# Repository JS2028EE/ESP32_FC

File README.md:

# ESP32_FC — ESP32-S3 quadcopter controller prototype

Rev B is a **70 × 65 mm, four-layer flight-controller hardware prototype** built around an ESP32-S3-WROOM-1-N8R8, a BMI088 SPI inertial sensor and a BMP280 barometer. It is intended for a quadcopter using a separate 4-in-1 ESC. The controller accepts a 3S–6S LiPo supply (9–25.2 V); motor current flows through the ESC.

**Status: unbuilt prototype. No flight firmware is included.** Design-file checks passed in KiCad 10.0.7 on 2026-10-15. No assembled board, power system, ESC interface, control loop or failsafe has been validated. These files support a small prototype order subject to manufacturer DFM acceptance; they do not establish flight or production readiness.

The preview omits some component bodies and is not a complete mechanical model.

## Download and open

1. [Download the complete repository ZIP](https://github.com/JS2028EE/ESP32_FC/archive/refs/heads/main.zip) and extract it.
2. Install KiCad 10 with its standard symbol, footprint and 3D-model libraries.
3. Open [ESP32_FC.kicad_pro](hardware/revB/ESP32_FC.kicad_pro) inside `hardware/revB`. Keep the whole folder together, including its five schematic sheets, local footprint library and `fp-lib-table`.
4. Open the schematic or PCB from KiCad's project manager. In PCB Editor, press **Alt+3** for the 3D Viewer. No standalone STEP assembly is supplied; some model bodies are missing.

For bare-board fabrication, use [ESP32_FC_RevB_Gerbers.zip](downloads/ESP32_FC_RevB_Gerbers.zip) and the [ordering instructions](hardware/revB/Order_Instructions.md). Do not upload the whole repository as a Gerber order. Rev A is superseded.

## Documentation

| Topic | Read |
|---|---|
| Purpose, architecture and intended performance | [System overview](docs/architecture.md) |
| What is missing and what remains untested | [Limitations](docs/limitations.md) |
| All connectors, GPIOs and ESC wiring | [Connections](docs/connections.md) |
| Component selection and buying parts | [Components](docs/components.md) |
| Power rails, load allocations and protection | [Power design](docs/power.md) |
| Firmware requirements and failsafes | [Firmware plan](docs/firmware.md) |
| Dimensions, mounting, layer stack and assembly | [Mechanical and manufacturing](docs/manufacturing.md) |
| Soldering and staged first power-up | [Assembly and bring-up](hardware/revB/Assembly_and_Bringup.md) |
| Checks performed and release boundary | [Validation](hardware/revB/Validation.md) |
| Datasheets and manufacturer references | [Sources](hardware/revB/Sources.md) |
| Revision history | [Change log](CHANGELOG.md) |
| File locations and reproducibility | [Repository guide](docs/repository-guide.md) |
| Contributions and reuse | [Contributing](CONTRIBUTING.md), [licensing status](THIRD_PARTY_NOTICES.md) |

## Main deliverables

- [Schematic PDF, five sheets](hardware/revB/Schematic.pdf) and [assembly drawing](hardware/revB/Assembly_Top.pdf).
- [Editable PCB](hardware/revB/ESP32_FC.kicad_pcb) and [root schematic](hardware/revB/ESP32_FC.kicad_sch).
- [Detailed BOM](hardware/revB/BOM.csv), [grouped shopping list](hardware/revB/Shopping_List.csv), [placement CSV](hardware/revB/Pick_and_place.csv) and [connector pad map](hardware/revB/Connector_Pin_Map.csv).
- [Raw fabrication outputs](hardware/revB/Fabrication), [DRC](hardware/revB/DRC.json), [ERC](hardware/revB/ERC.json), [audit summary](hardware/revB/Design_Audit.json) and [SHA-256 manifest](SHA256SUMS.json).

## Key integration constraints

J5 is a custom **2.54 mm** header and needs a function-matched harness. The reference Holybro Tekko32 F4 4in1 50A AM32 (SKU31102) supports **4S–6S**, so the reference combination starts at 4S. USB is full-speed **12 Mbps, data-only** and needs battery/bench power. Serial logic is 3.3 V. Motor outputs are unidirectional; bidirectional DShot is unsupported. No independent hardware watchdog removes motor enable after a software freeze.

High clock speed is not evidence of a deterministic flight-control loop. A 1 kHz loop is an initial firmware target that must be measured under worst-case load. No stock Betaflight, PX4 or ArduPilot binary is assumed to support this custom board.

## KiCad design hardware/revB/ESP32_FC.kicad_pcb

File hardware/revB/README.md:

# ESP32-S3 flight-controller bench prototype - Rev B

This is the current editable KiCad 10 project for a 70 x 65 mm, four-layer controller, with an ESP32-S3-WROOM-1-N8R8, BMI088 SPI IMU, BMP280 barometer and a separate 4-in-1 ESC. The FC supply accepts a 3S-6S LiPo (9-25.2 V). Motor current stays on the ESC.

**Order status: prepared for a small bare-board prototype run to Order_Instructions.md.** This is an unbuilt design, not validated flight hardware. KiCad checks and the source/PCB audit pass. The manufacturer still must accept the uploaded fabrication data and requested stackup through its normal DFM process. Physical regulator, USB, sensor and flight validation cannot be completed in software. No flight firmware is included.

Use the Rev B ZIP and Gerbers. The earlier Rev A packages are superseded for this build.

## Open the design

Extract the entire project ZIP. Open ESP32_FC.kicad_pro, then ESP32_FC.kicad_sch or ESP32_FC.kicad_pcb. Keep all five schematic files and FC_Prototype.pretty together. In PCB Editor, Alt+3 opens the native 3D Viewer using installed KiCad 10 model libraries. A separate STEP assembly is not bundled. Some bodies are absent in the preview, including the USB connector and the new fuse; model availability does not affect the fabrication data. PCB_Preview.png is a partial 3D illustration, not an exact assembly envelope check.

## What changed

- Added Q3 and R46: USB VBUS now drives an isolated MOSFET gate. GPIO16 is pulled to the MCU's own 3.3 V rail and reads LOW when USB VBUS is present. USB cannot feed the MCU rail through the previous VBUS sense divider. USB remains data-only; battery power is required.
- Added C27, a real 47uF/50V Panasonic radial electrolytic for input damping. C6/C7 are sourced 2.2uF/100V ceramic bypass capacitors, replacing the unsourced 47uF/50V ceramic requirement.
- Selected Littelfuse 0476001.MR, 1 A, with a documented 10 kA interrupt rating at 86 VDC. Its 2410 lands follow the manufacturer drawing; do not fit the old 1206 fuse. This protects the FC branch, not the motor circuit.
- Selected DMN2056U-7 MOSFETs, with on-resistance specified at low gate voltage, for output gating, buzzer and USB detection.
- Changed R21 to 150k. Battery ADC is VIN_PROT/16; 25.2 V at the protected input gives 1.575 V. Calibrate the diode drop and ADC gain in firmware.
- Shortened regulator bootstrap, bypass and feedback routes; connected C8 directly to U3 VIN/PGND. Recorded a JLC04161H-3313 four-layer stackup.
- Rerouted USB D+/D- from ESD protection to the series resistors on the front layer over the uninterrupted ground plane, removing four vias. Those two sections measure 12.960 and 12.945 mm. USB is full speed, 12 Mbps; this is not 480 Mbps USB high speed. Impedance is not a measured/certified result.
- Completed the BOM with selected component numbers, provided a grouped shopping list and a coordinate-based connector map. Stock/price and authorized distributor availability should be checked when buying; substitutions require matching the actual package and electrical characteristics.
- Applied 1.0 mm text height and 0.15 mm text stroke to printed references. 88 references fit on silkscreen; others remain on the assembly layer. Use Assembly_Top.pdf for placement.

## Processor pin assignment

| Function | ESP32-S3 GPIO | Notes |
|---|---|---|
| Battery ADC | 1 | ADC1; senses protected input after D1 |
| ESC current ADC | 2 | ADC1; 2:1 divider, 0-5 V analog input only |
| Motor 1 / 2 / 3 / 4 | 4 / 5 / 6 / 15 | Through U8 and 33-ohm series resistors |
| Gyro / accel data-ready | 7 / 8 | BMI088 INT3 / INT1 |
| Gyro / accel CS | 9 / 10 | Active low; external 10k pull-ups |
| IMU MOSI / SCK / MISO | 11 / 12 / 13 | Separate from the flash/PSRAM interface |
| USB VBUS sense | 16 | Active-low, isolated by Q3 |
| Receiver TX / RX | 17 / 18 | Flight-controller perspective; remapped UART1 |
| USB D- / D+ | 19 / 20 | 22-ohm series termination and USBLC6 protection |
| Arm output | 21 | HIGH enables motor buffers; LOW disables |
| I2C SDA / SCL | 38 / 39 | 4.7k pull-ups to sensor rail |
| Status LED | 40 | HIGH turns LED on |
| Auxiliary GPIO | 41 | Exposed on J9 |
| Active buzzer | 42 | Drives Q2; external 5 V active buzzer <=30 mA |
| Debug TX / RX | 43 / 44 | UART0; includes boot messages |
| GPS TX / RX | 47 / 48 | Remapped UART2 |
| Boot / voltage straps | 0 / 45 / 46 | Boot pull-up, GPIO45/46 pull-downs |

GPIO3 and GPIO14 are unused. GPIO35/36/37 are reserved. Critical sensor buffers and control code should use internal SRAM; do not depend on PSRAM access latency for the real-time loop. A reasonable initial firmware target is a 1 kHz gyro-triggered loop, subject to measured worst-case latency. Hardware peripherals should generate motor timing. Radio operation, flash writes, USB, and navigation tasks must be qualified for scheduling interference.

## Connectors and ESC

Connector_Pin_Map.csv gives every numbered header pad and its location as viewed from the component side, with the antenna at the top. It is the definitive pad-to-net map. J5 uses 2.54 mm headers, not the 1 mm connector fitted to commercial ESCs. A custom harness is required.

| Connector | Pins in numeric order |
|---|---|
| J2 | battery+, GND; FC branch supply only |
| J3 | GND, sensor 3.3V, SDA, SCL |
| J4 | ARM_GATE, GND; short to force outputs disabled |
| J5 | GND, battery+, motor1, motor2, motor3, motor4, analog current, telemetry breakout |
| J6 | GND, 5V, FC RX, FC TX; receiver |
| J7 | GND, 5V, FC RX, FC TX; GPS |
| J8 | GND, digital 3.3V, FC RX0, FC TX0; debug |
| J9 | GND, digital 3.3V, GPIO41, telemetry breakout |
| J10 | 5V, buzzer low-side drain |

J2 and J5 battery pins are the same node. Use only one FC battery feed. Receiver/GPS supply is 5 V but all MCU serial logic is 3.3 V. Do not connect independently powered serial devices or a 5 V UART adapter without checking powered-off and logic-voltage compatibility. J5 analog current accepts 0-5 V and divides it by two. Telemetry is only a passive breakout to J9, not a configured MCU UART.

The reference ESC is Holybro Tekko32 F4 4in1 50A AM32, SKU31102; see ESC_Wiring.md. It supports **4S-6S**, so use a 4S pack for that reference combination. The FC itself retains its 3S-6S input range; using 3S requires an ESC explicitly rated for 3S. This recommendation does not establish motor/propeller compatibility; motor current requirements must be matched separately.

## Power and firmware limits

The 5 V regulator is rated 1 A; it supplies all downstream rails and peripherals. Initial allocations: digital 3.3 V <=0.70 A, sensor 3.3 V <=0.05 A, external 5 V <=0.25 A including buzzer. They correspond to about 0.84 A from 5 V at 85% digital-buck efficiency. These are design allocations, not measured continuous ratings. Begin bench tests with smaller loads and verify temperature and transients before approaching them. No VTX/air-unit supply is provided. External active buzzer <=30 mA.

The N8R8 module is specified by Espressif for ambient temperatures up to 65 C, which is lower than the 85 C rating of several passive parts. No board temperature operating range is qualified. Avoid inductors heating the sensors/module. Use the barometer without blocking its pressure port.

Q1 and U8 disable motor outputs during MCU reset. J4 is a physical disable strap. A frozen MCU that leaves ARM asserted is not stopped by independent watchdog hardware: firmware must configure watchdog reset, receiver timeout, arming checks, brownout handling and motor timing. Start with unidirectional DShot300 for ESC bring-up; bidirectional DShot is unsupported through U8. No stock Betaflight/PX4/ArduPilot binary is assumed to work on this custom ESP32 board.

## Before applying power

Follow Assembly_and_Bringup.md. Solder paste and hot-air/reflow are required for the LGA sensors and exposed-pad regulator. Observe component moisture/reflow limits. All components mount on the front; C27 and headers are soldered after reflow. The 6.3 mm diameter C27 body is 11.2 mm tall. Inspect soldering and check resistance to ground before using a current-limited bench supply. Fit the kill strap; leave ESC, motors, receiver and GPS disconnected initially.

## References

See Sources.md for manufacturer documents used for this revision, Order_Instructions.md for fabrication settings and Validation.md for the actual checks and their limits.

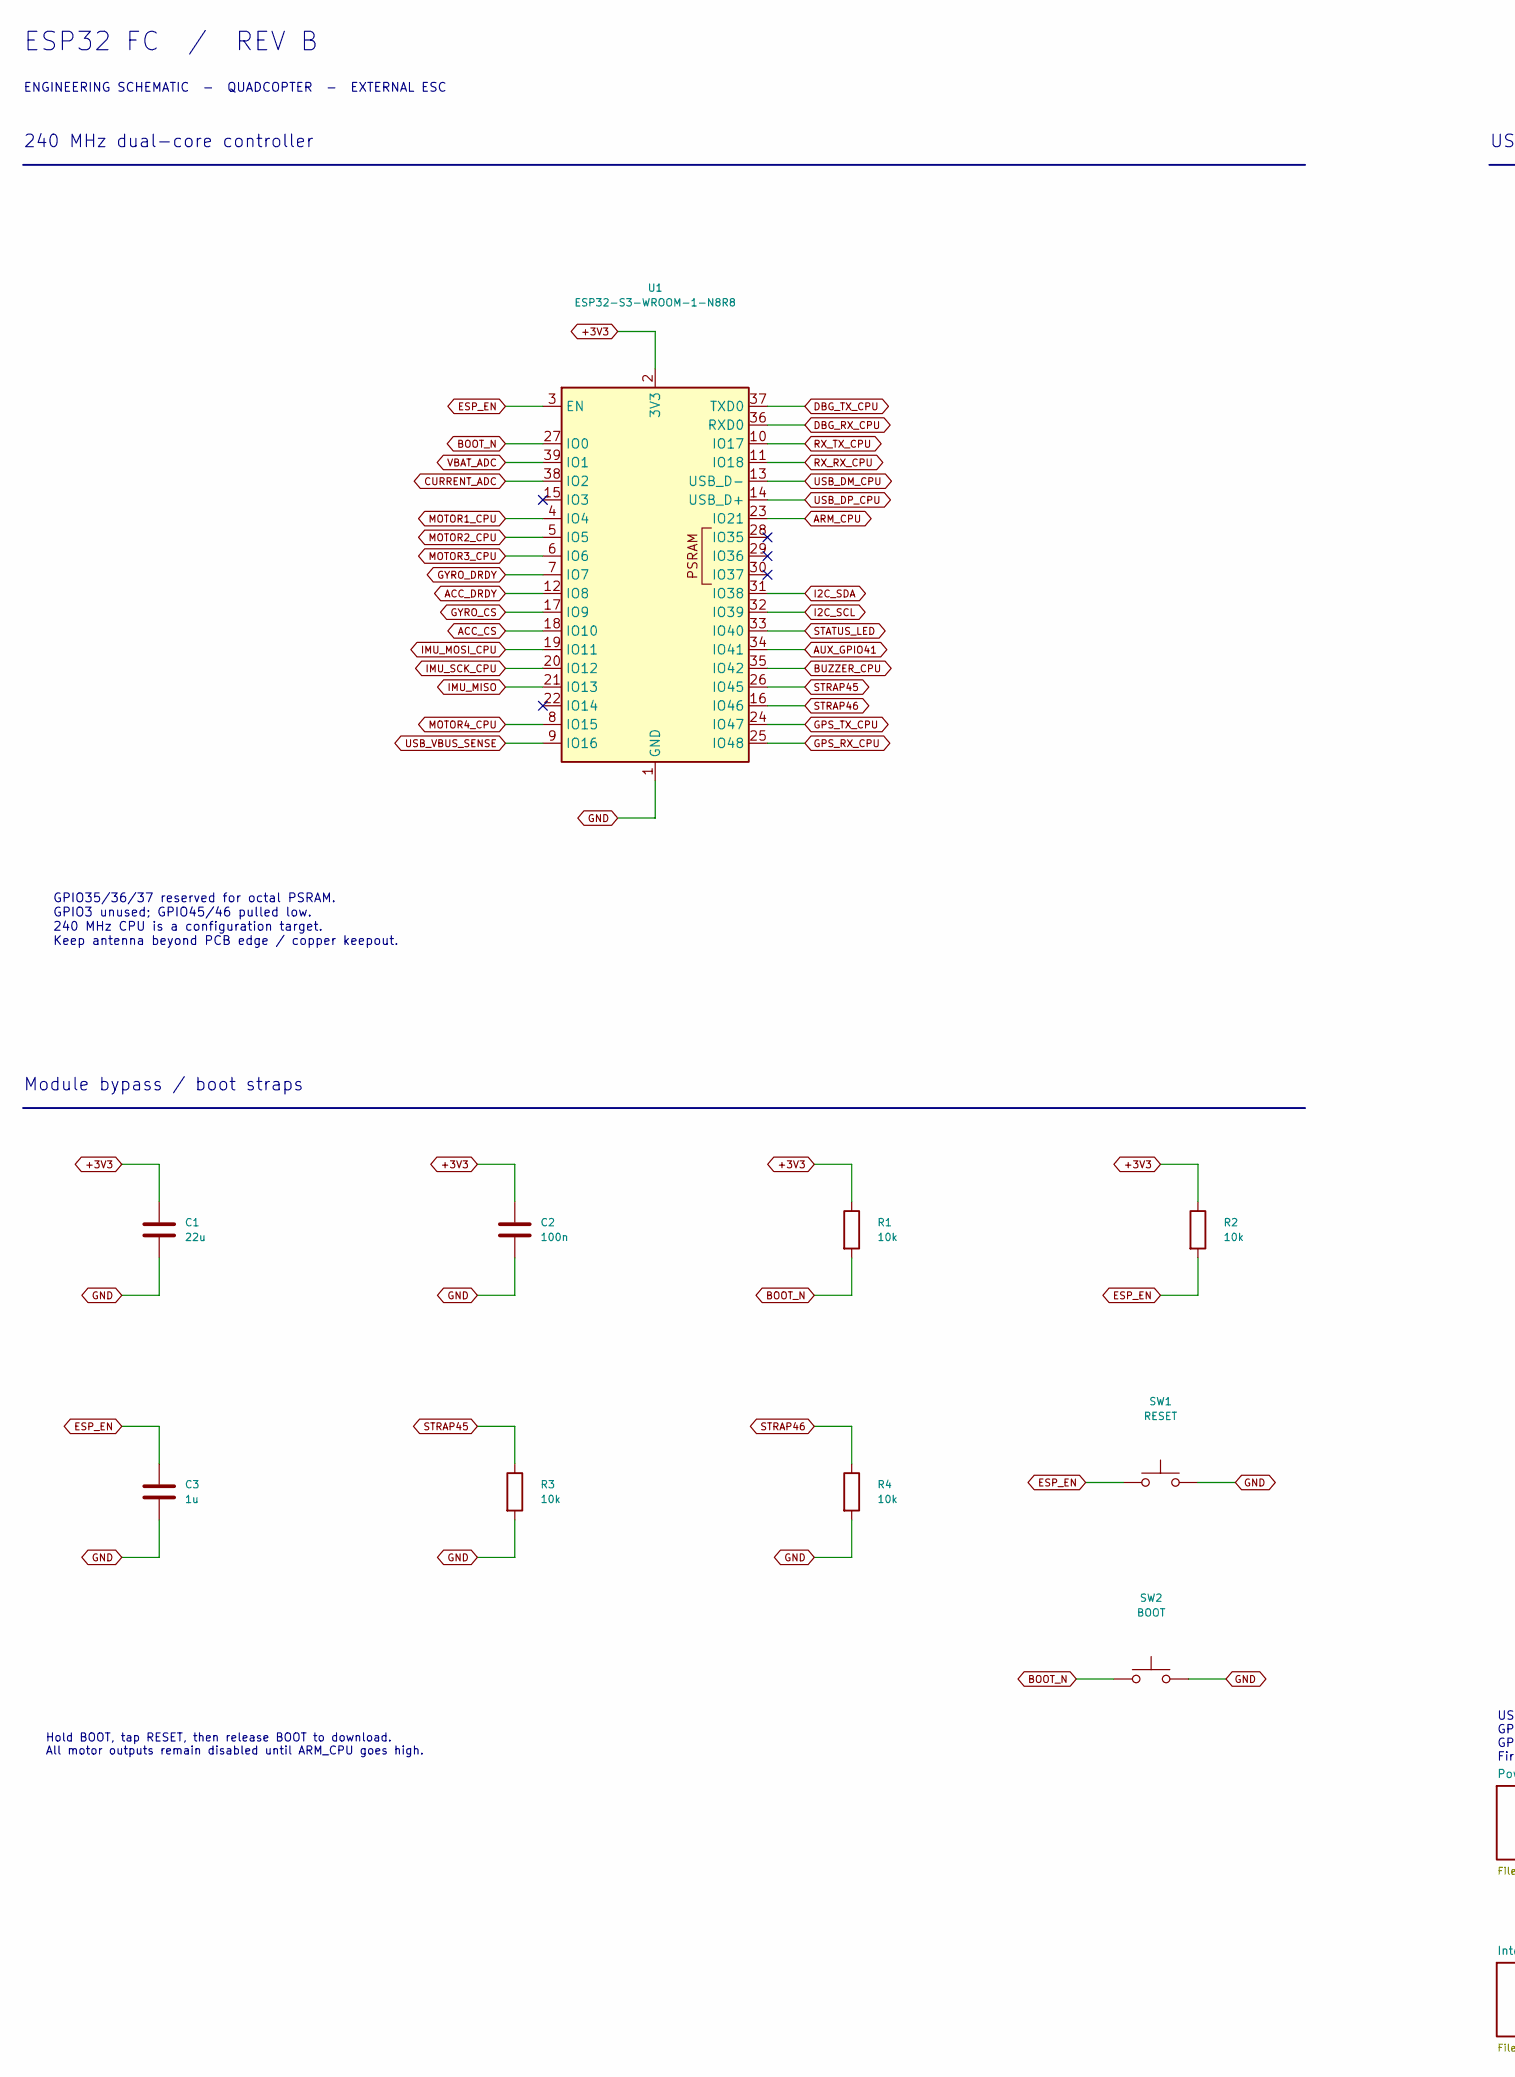
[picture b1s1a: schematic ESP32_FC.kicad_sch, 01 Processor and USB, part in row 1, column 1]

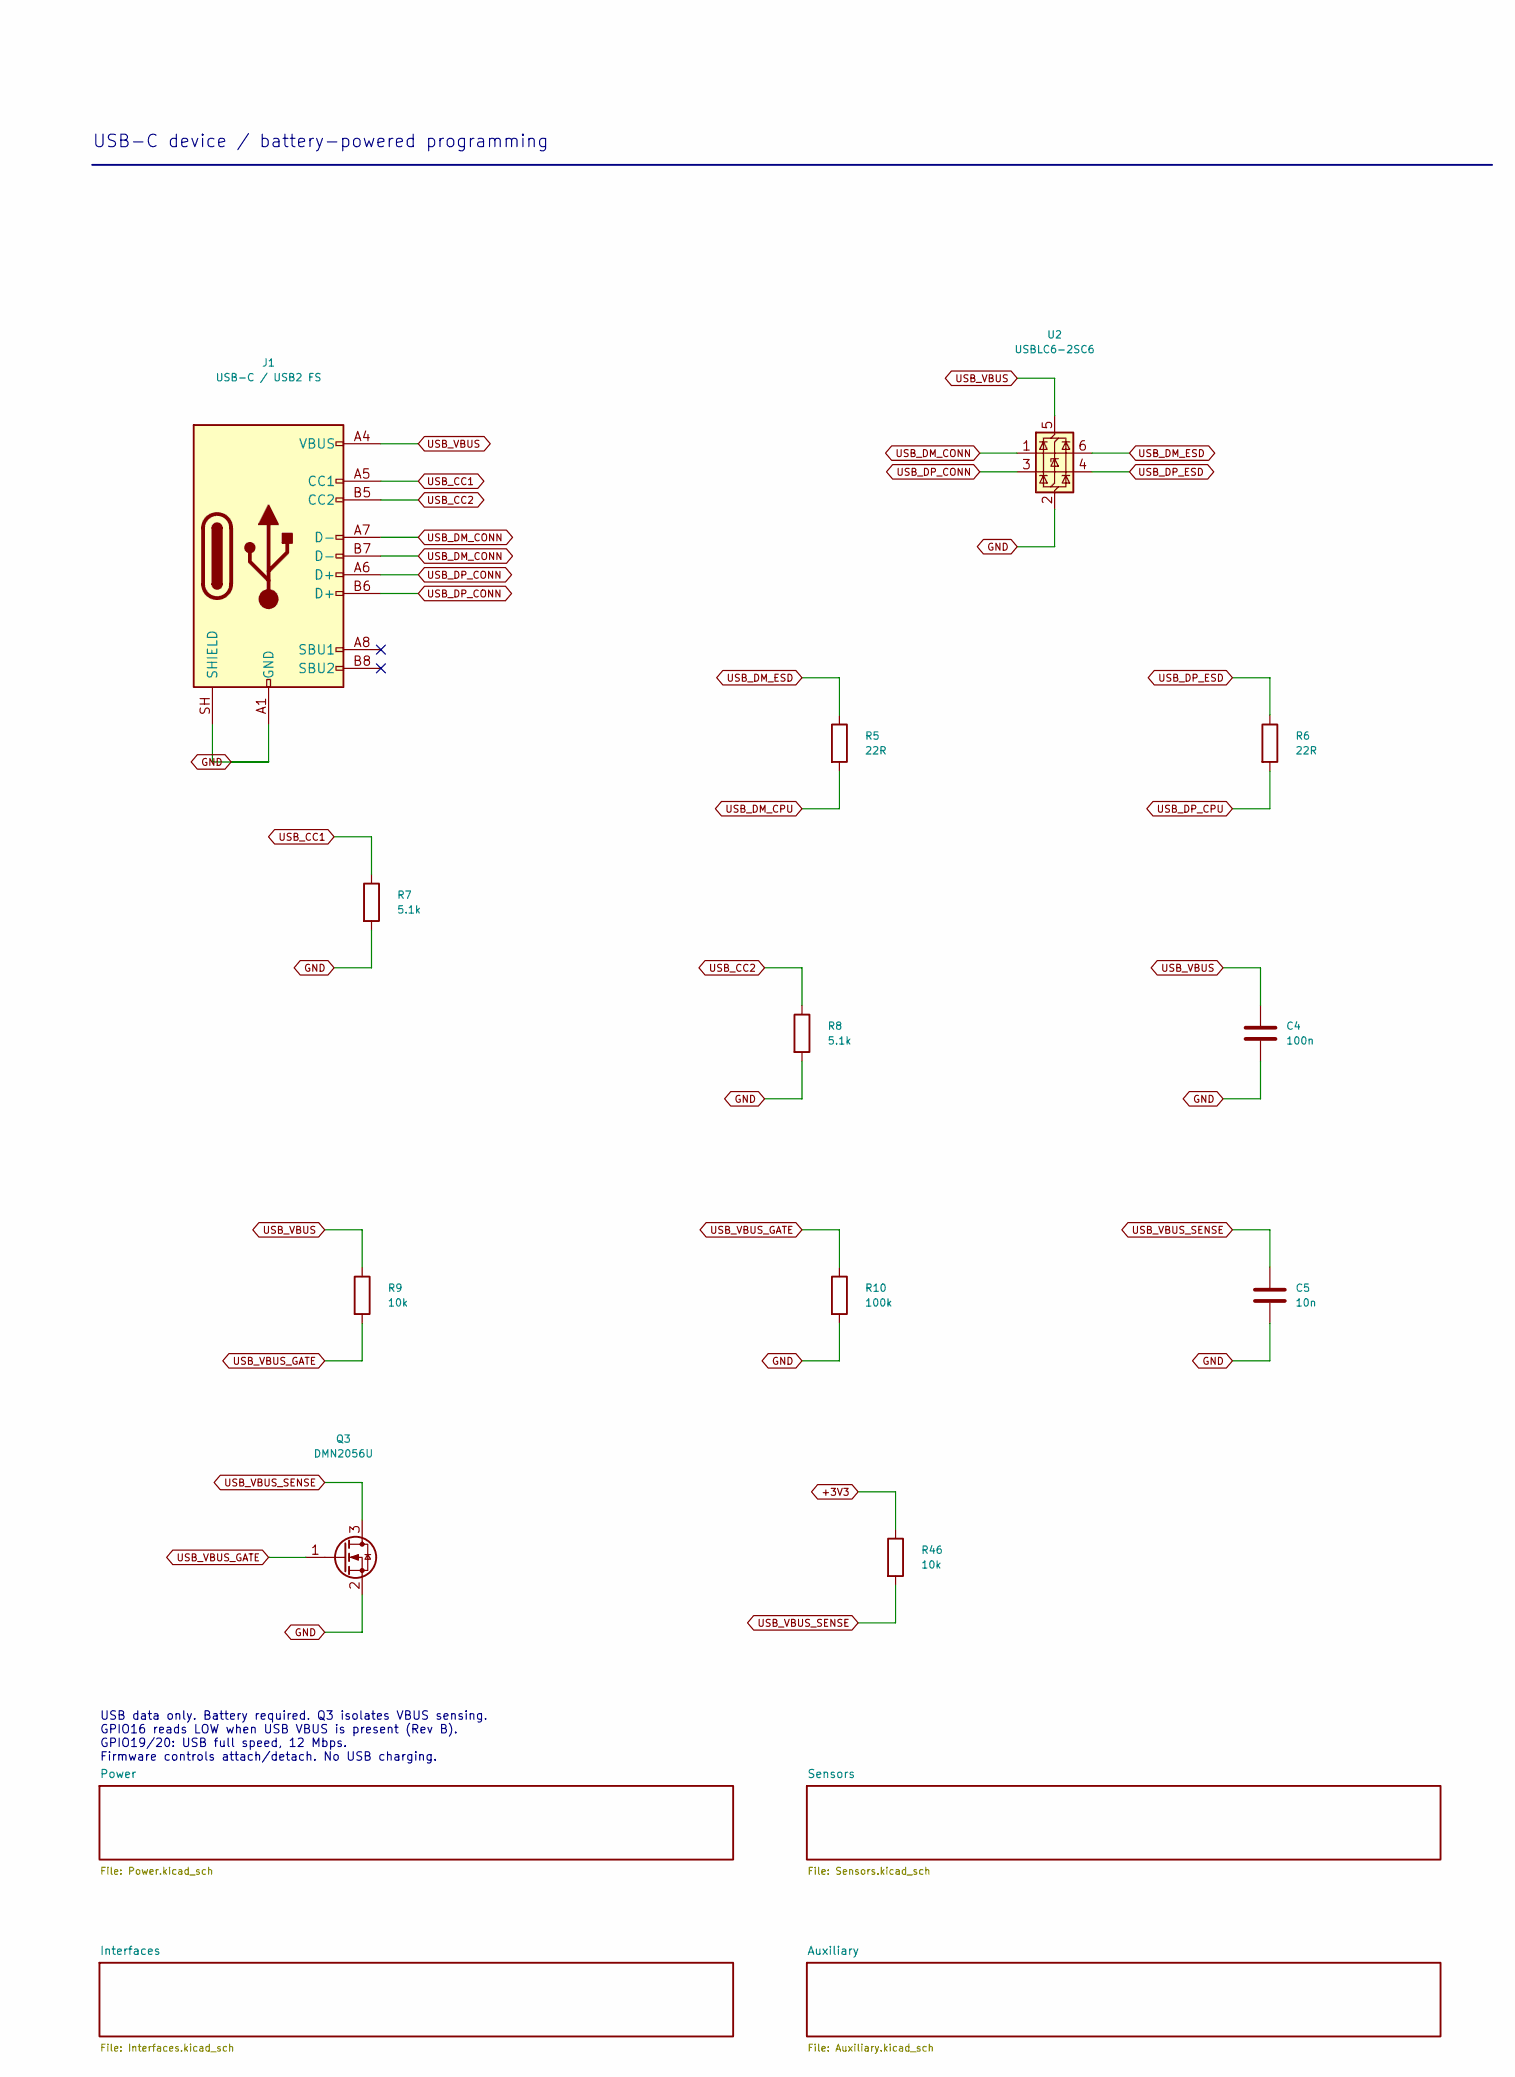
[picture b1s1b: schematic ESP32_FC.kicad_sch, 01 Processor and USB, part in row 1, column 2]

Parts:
C1: 22u; C_0805_2012Metric; MPN GRM21BR61C226ME44L
C2, C4: 100n; C_0603_1608Metric; MPN GRM188R71C104KA01D
C3: 1u; C_0603_1608Metric; MPN GRM188R71C105KA12D
C5: 10n; C_0603_1608Metric; MPN GRM188R71H103KA01D
J1: USB-C / USB2 FS; USB_C_HRO_Edge; MPN TYPE-C-31-M-12
Q3: DMN2056U; SOT-23; MPN DMN2056U-7
R1, R2, R3, R4, R9, R46: 10k; R_0603_1608Metric; MPN RC0603FR-0710KL
R5, R6: 22R; R_0603_1608Metric; MPN RC0603FR-0722RL
R7, R8: 5.1k; R_0603_1608Metric; MPN RC0603FR-075K1L
R10: 100k; R_0603_1608Metric; MPN RC0603FR-07100KL
SW1: RESET; SW_SPST_TL3342; MPN TL3342F160QG
SW2: BOOT; SW_SPST_TL3342; MPN TL3342F160QG
U1: ESP32-S3-WROOM-1-N8R8; ESP32_S3_WROOM_Edge; MPN ESP32-S3-WROOM-1-N8R8
U2: USBLC6-2SC6; SOT-23-6; MPN USBLC6-2SC6

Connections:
+3V3: C1.1, C2.1, R1.1, R2.1, R46.1, U1.2 (3V3); also elsewhere on the board
ACC_CS: U1.18 (IO10); also elsewhere on the board
ACC_DRDY: U1.12 (IO8); also elsewhere on the board
ARM_CPU: U1.23 (IO21); also elsewhere on the board
AUX_GPIO41: U1.34 (IO41); also elsewhere on the board
BOOT_N: R1.2, SW2.1, U1.27 (IO0)
BUZZER_CPU: U1.35 (IO42); also elsewhere on the board
CURRENT_ADC: U1.38 (IO2); also elsewhere on the board
DBG_RX_CPU: U1.36 (RXD0); also elsewhere on the board
DBG_TX_CPU: U1.37 (TXD0); also elsewhere on the board
ESP_EN: C3.1, R2.2, SW1.1, U1.3 (EN)
GND: C1.2, C2.2, C3.2, C4.2, C5.2, J1.A1 (GND), J1.A12 (GND), J1.B1 (GND), J1.B12 (GND), J1.SH (SHIELD), Q3.2 (S), R3.2, R4.2, R7.2, R8.2, R10.2, SW1.2, SW2.2, U1.1 (GND), U1.40 (GND), U1.41 (GND), U2.2 (GND); also elsewhere on the board
GPS_RX_CPU: U1.25 (IO48); also elsewhere on the board
GPS_TX_CPU: U1.24 (IO47); also elsewhere on the board
GYRO_CS: U1.17 (IO9); also elsewhere on the board
GYRO_DRDY: U1.7 (IO7); also elsewhere on the board
I2C_SCL: U1.32 (IO39); also elsewhere on the board
I2C_SDA: U1.31 (IO38); also elsewhere on the board
IMU_MISO: U1.21 (IO13); also elsewhere on the board
IMU_MOSI_CPU: U1.19 (IO11); also elsewhere on the board
IMU_SCK_CPU: U1.20 (IO12); also elsewhere on the board
MOTOR1_CPU: U1.4 (IO4); also elsewhere on the board
MOTOR2_CPU: U1.5 (IO5); also elsewhere on the board
MOTOR3_CPU: U1.6 (IO6); also elsewhere on the board
MOTOR4_CPU: U1.8 (IO15); also elsewhere on the board
RX_RX_CPU: U1.11 (IO18); also elsewhere on the board
RX_TX_CPU: U1.10 (IO17); also elsewhere on the board
STATUS_LED: U1.33 (IO40); also elsewhere on the board
STRAP45: R3.1, U1.26 (IO45)
STRAP46: R4.1, U1.16 (IO46)
USB_CC1: J1.A5 (CC1), R7.1
USB_CC2: J1.B5 (CC2), R8.1
USB_DM_CONN: J1.A7 (D-), J1.B7 (D-), U2.1 (I/O1)
USB_DM_CPU: R5.2, U1.13 (USB_D-)
USB_DM_ESD: R5.1, U2.6 (I/O1)
USB_DP_CONN: J1.A6 (D+), J1.B6 (D+), U2.3 (I/O2)
USB_DP_CPU: R6.2, U1.14 (USB_D+)
USB_DP_ESD: R6.1, U2.4 (I/O2)
USB_VBUS: C4.1, J1.A4 (VBUS), J1.A9 (VBUS), J1.B4 (VBUS), J1.B9 (VBUS), R9.1, U2.5 (VBUS)
USB_VBUS_GATE: Q3.1 (G), R9.2, R10.1
USB_VBUS_SENSE: C5.1, Q3.3 (D), R46.2, U1.9 (IO16)
VBAT_ADC: U1.39 (IO1); also elsewhere on the board

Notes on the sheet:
ESP32 FC / REV B
ENGINEERING SCHEMATIC - QUADCOPTER - EXTERNAL ESC
240 MHz dual-core controller
GPIO35/36/37 reserved for octal PSRAM. GPIO3 unused; GPIO45/46 pulled low. 240 MHz CPU is a configuration target. Keep antenna beyond PCB edge / copper keepout.
Module bypass / boot straps
Hold BOOT, tap RESET, then release BOOT to download. All motor outputs remain disabled until ARM_CPU goes high.
USB-C device / battery-powered programming
USB data only. Battery required. Q3 isolates VBUS sensing. GPIO16 reads LOW when USB VBUS is present (Rev B). GPIO19/20: USB full speed, 12 Mbps. Firmware controls attach/detach. No USB charging.

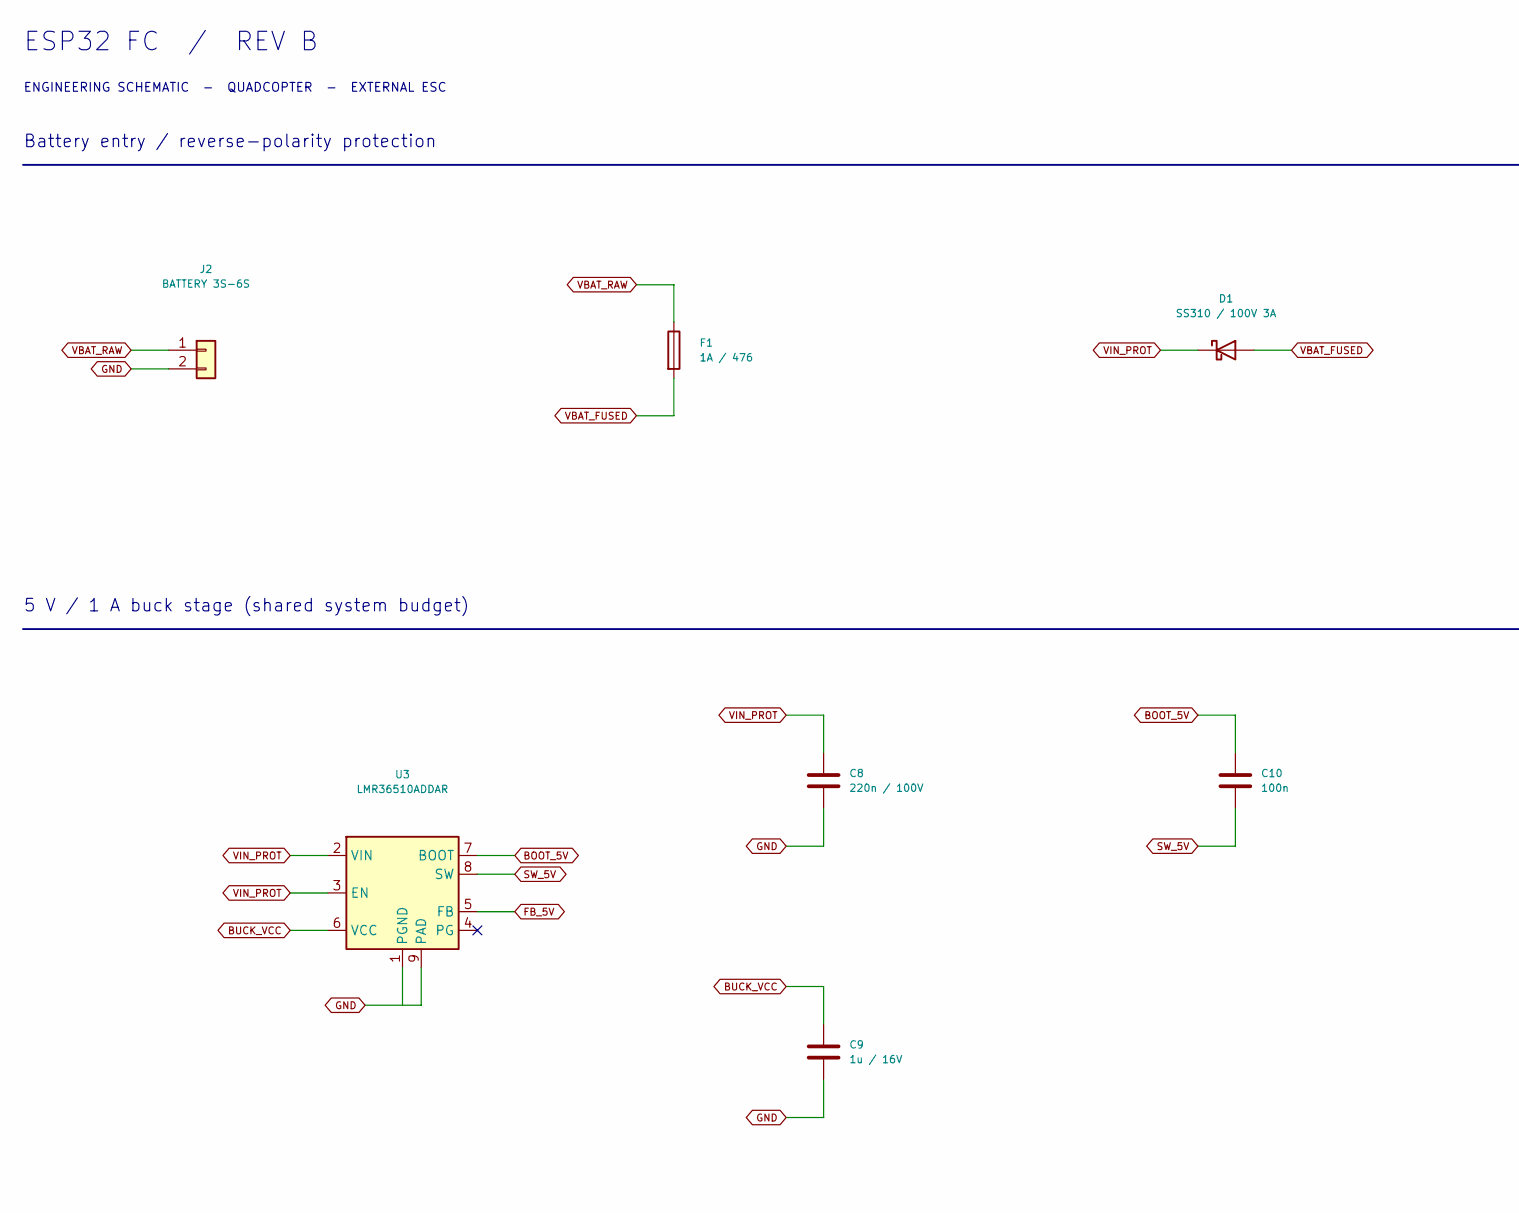
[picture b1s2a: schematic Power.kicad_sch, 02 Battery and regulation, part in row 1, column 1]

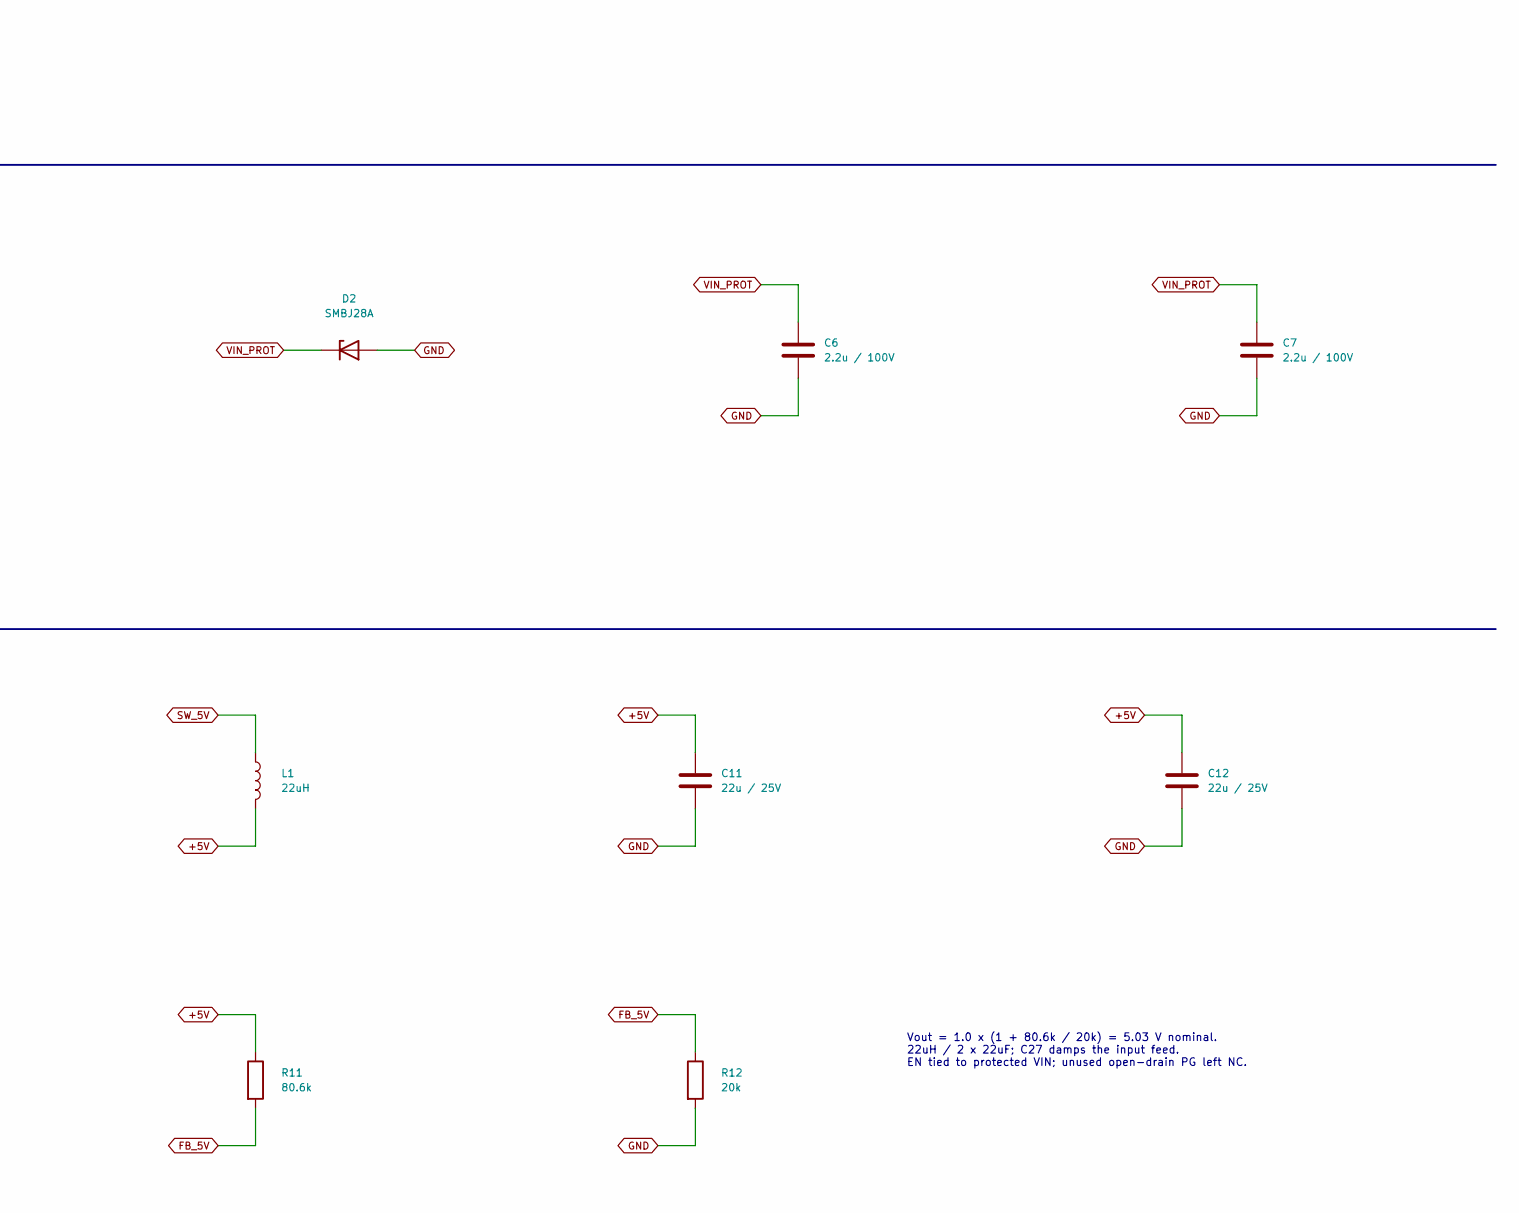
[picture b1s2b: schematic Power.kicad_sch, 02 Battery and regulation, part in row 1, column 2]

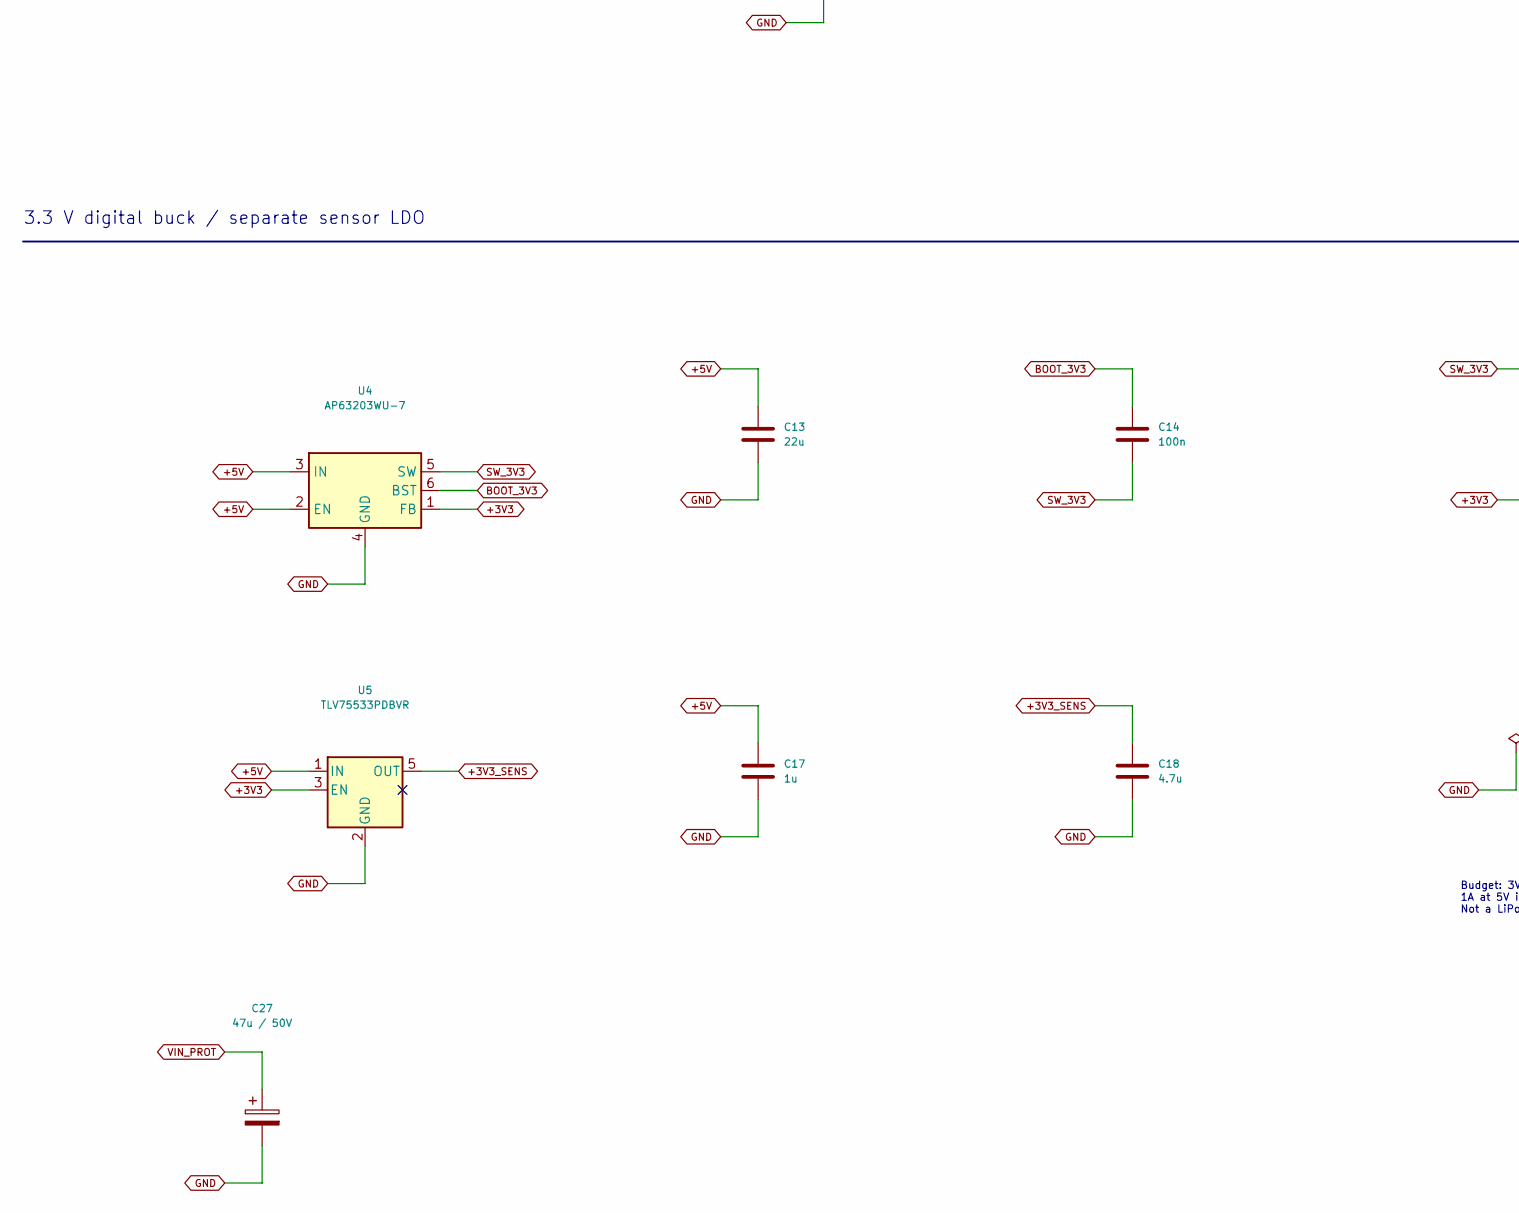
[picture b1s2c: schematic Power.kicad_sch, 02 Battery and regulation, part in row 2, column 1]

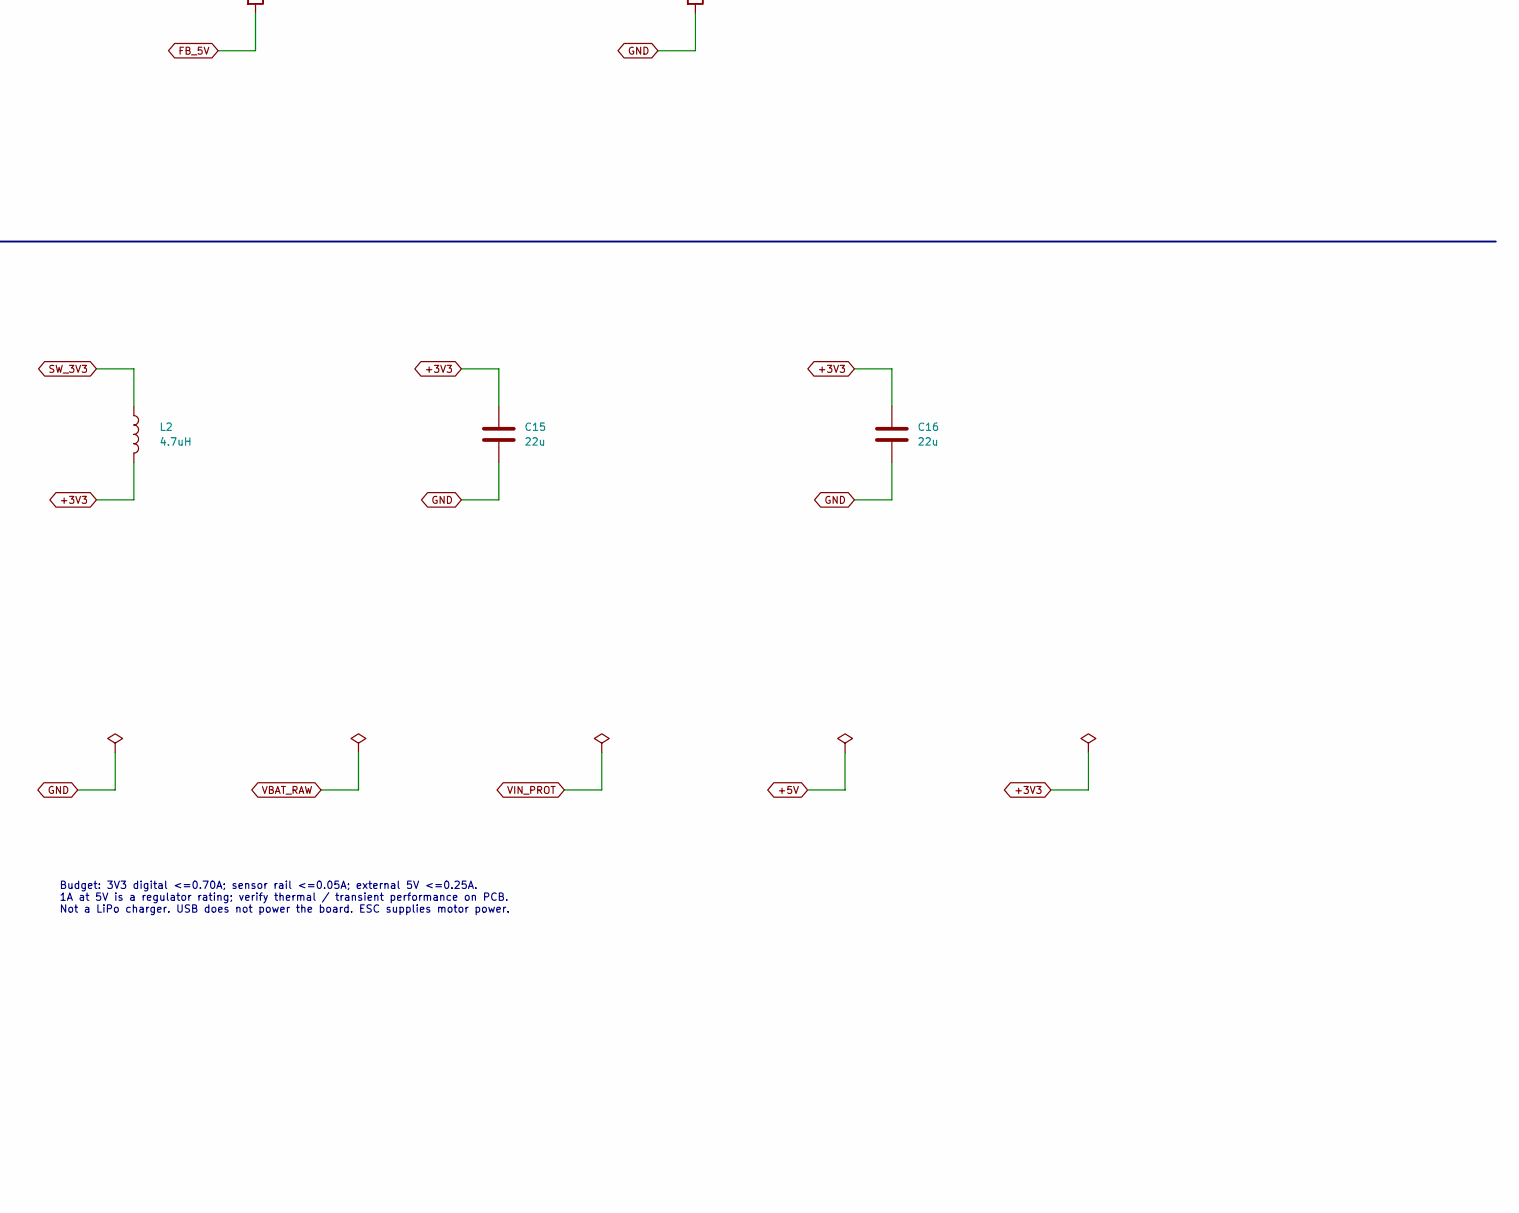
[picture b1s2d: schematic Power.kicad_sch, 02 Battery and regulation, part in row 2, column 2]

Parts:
C6, C7: 2.2u / 100V; C_1210_3225Metric; MPN GRM32ER72A225KA35L
C8: 220n / 100V; C_0805_2012Metric; MPN C0805C224K1RACTU
C9: 1u / 16V; C_0603_1608Metric; MPN GRM188R71C105KA12D
C10, C14: 100n; C_0603_1608Metric; MPN GRM188R71C104KA01D
C11, C12: 22u / 25V; C_1210_3225Metric; MPN GRM32ER71E226KE15L
C13, C15, C16: 22u; C_0805_2012Metric; MPN GRM21BR61C226ME44L
C17: 1u; C_0603_1608Metric; MPN GRM188R71C105KA12D
C18: 4.7u; C_0603_1608Metric; MPN GRM188R61C475KE11D
C27: 47u / 50V; CP_Radial_D6.3mm_P2.50mm; MPN EEUFR1H470
D1: SS310 / 100V 3A; D_SMA; MPN SS310-13-F
D2: SMBJ28A; D_SMB; MPN SMBJ28A-13-F
F1: 1A / 476; Fuse_Littelfuse_476; MPN 0476001.MR
J2: BATTERY 3S-6S; SolderWire-1sqmm_1x02_P5.4mm_D1.4mm_OD2.7mm; MPN WIRE CONNECTION - NO FITTED PART
L1: 22uH; L_Bourns_SRP6060FA; MPN SRP6060FA-220M
L2: 4.7uH; L_Bourns_SRP5030T; MPN SRP5030T-4R7M
R11: 80.6k; R_0603_1608Metric; MPN RC0603FR-0780K6L
R12: 20k; R_0603_1608Metric; MPN RC0603FR-0720KL
U3: LMR36510ADDAR; Texas_HTSOP-8-1EP_3.9x4.9mm_P1.27mm_EP2.95x4.9mm_Mask2.4x3.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; MPN LMR36510ADDAR
U4: AP63203WU-7; TSOT-23-6; MPN AP63203WU-7
U5: TLV75533PDBVR; SOT-23-5; MPN TLV75533PDBVR

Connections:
+3V3: C15.1, C16.1, L2.2, U4.1 (FB), U5.3 (EN); also elsewhere on the board
+3V3_SENS: C18.1, U5.5 (OUT); also elsewhere on the board
+5V: C11.1, C12.1, C13.1, C17.1, L1.2, R11.1, U4.2 (EN), U4.3 (IN), U5.1 (IN); also elsewhere on the board
BOOT_3V3: C14.1, U4.6 (BST)
BOOT_5V: C10.1, U3.7 (BOOT)
BUCK_VCC: C9.1, U3.6 (VCC)
FB_5V: R11.2, R12.1, U3.5 (FB)
GND: C6.2, C7.2, C8.2, C9.2, C11.2, C12.2, C13.2, C15.2, C16.2, C17.2, C18.2, C27.2, D2.2 (A), J2.2, R12.2, U3.1 (PGND), U3.9 (PAD), U4.4 (GND), U5.2 (GND); also elsewhere on the board
SW_3V3: C14.2, L2.1, U4.5 (SW)
SW_5V: C10.2, L1.1, U3.8 (SW)
VBAT_FUSED: D1.2 (A), F1.2
VBAT_RAW: F1.1, J2.1; also elsewhere on the board
VIN_PROT: C6.1, C7.1, C8.1, C27.1, D1.1 (K), D2.1 (K), U3.2 (VIN), U3.3 (EN); also elsewhere on the board

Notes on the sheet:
ESP32 FC / REV B
ENGINEERING SCHEMATIC - QUADCOPTER - EXTERNAL ESC
Battery entry / reverse-polarity protection
5 V / 1 A buck stage (shared system budget)
Vout = 1.0 x (1 + 80.6k / 20k) = 5.03 V nominal. 22uH / 2 x 22uF; C27 damps the input feed. EN tied to protected VIN; unused open-drain PG left NC.
3.3 V digital buck / separate sensor LDO
Budget: 3V3 digital <=0.70A; sensor rail <=0.05A; external 5V <=0.25A. 1A at 5V is a regulator rating; verify thermal / transient performance on PCB. Not a LiPo charger. USB does not power the board. ESC supplies motor power.
